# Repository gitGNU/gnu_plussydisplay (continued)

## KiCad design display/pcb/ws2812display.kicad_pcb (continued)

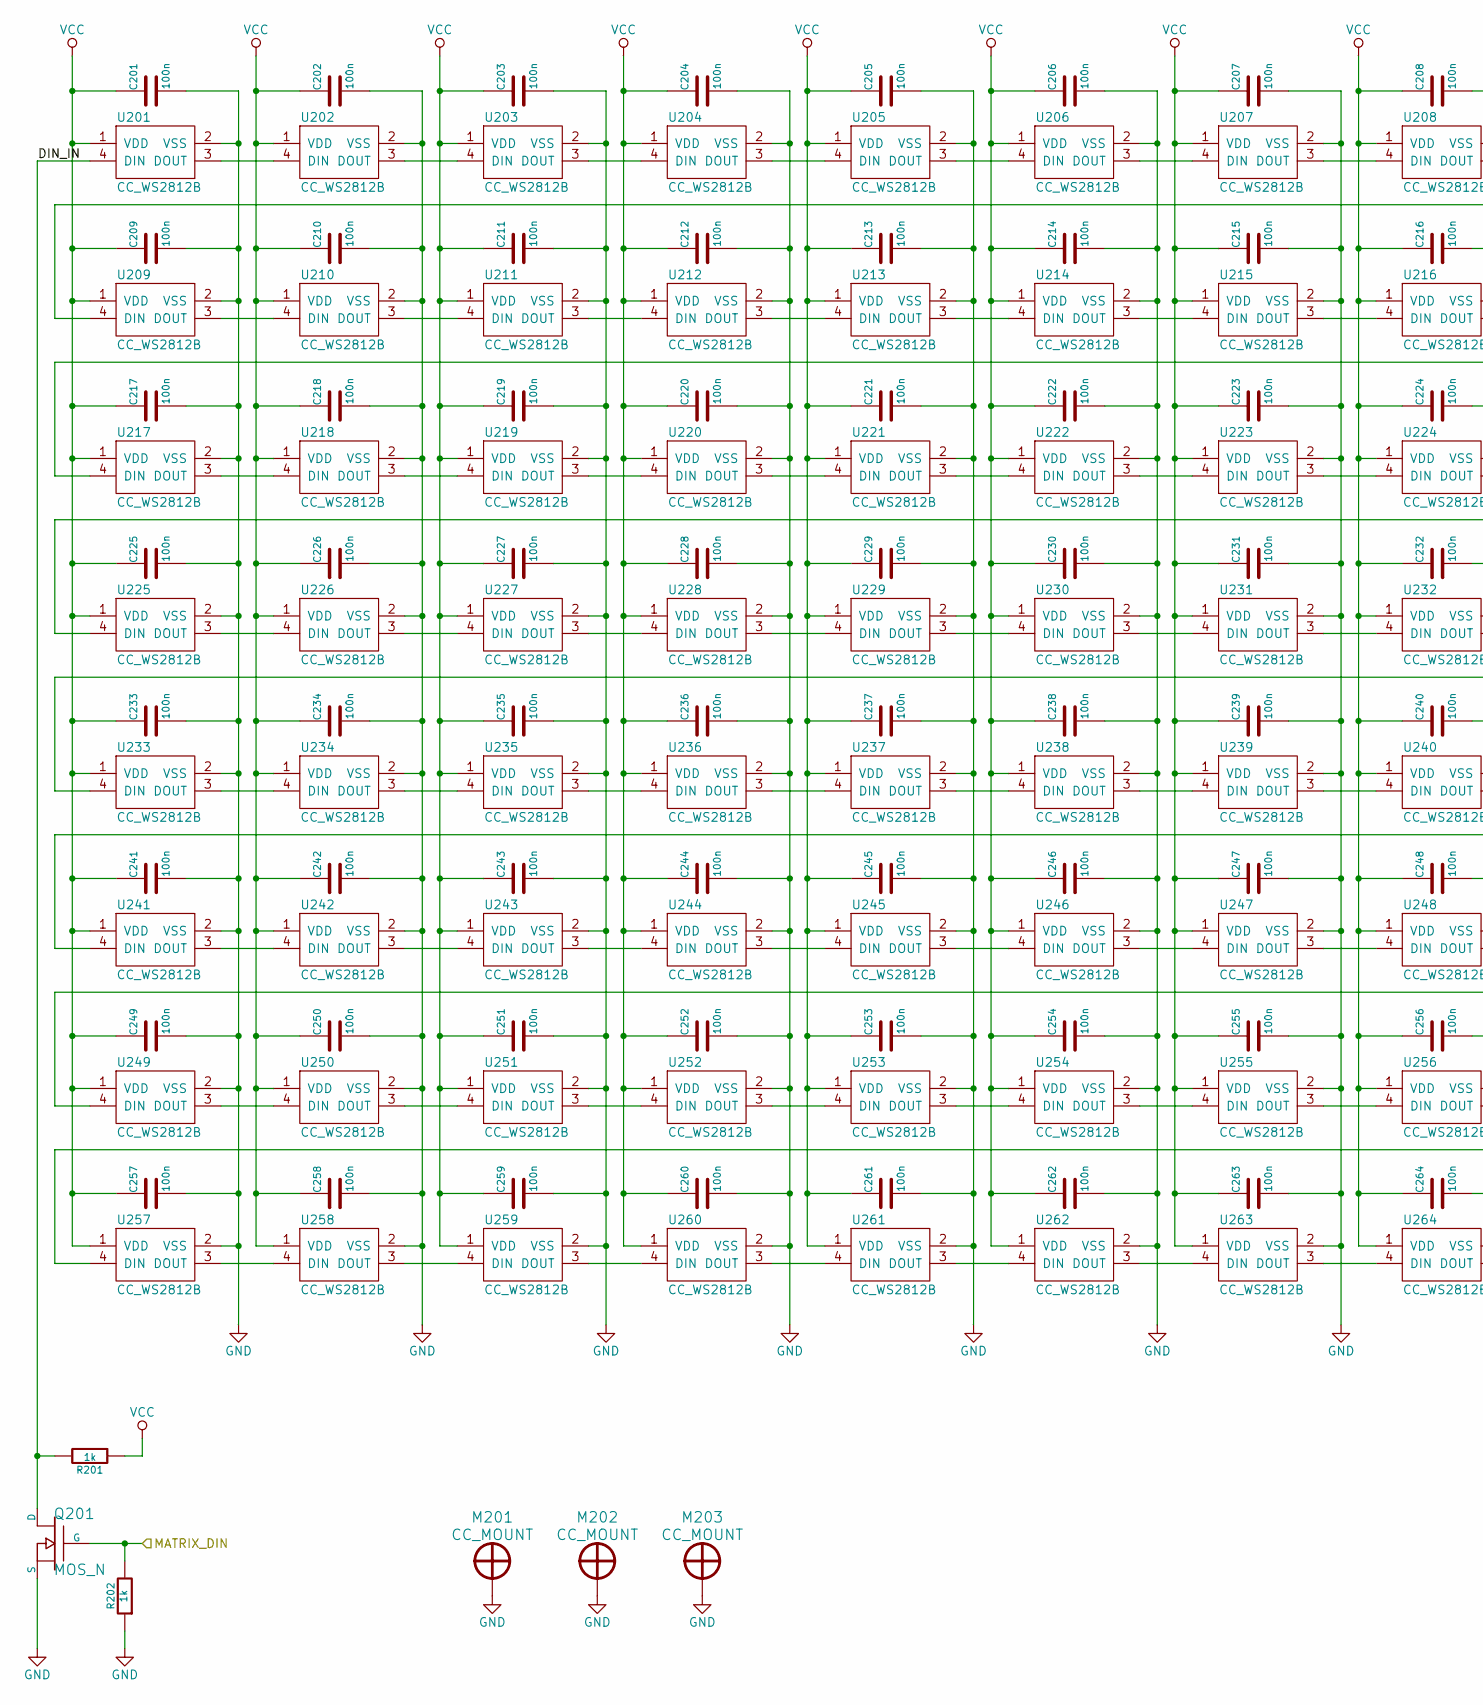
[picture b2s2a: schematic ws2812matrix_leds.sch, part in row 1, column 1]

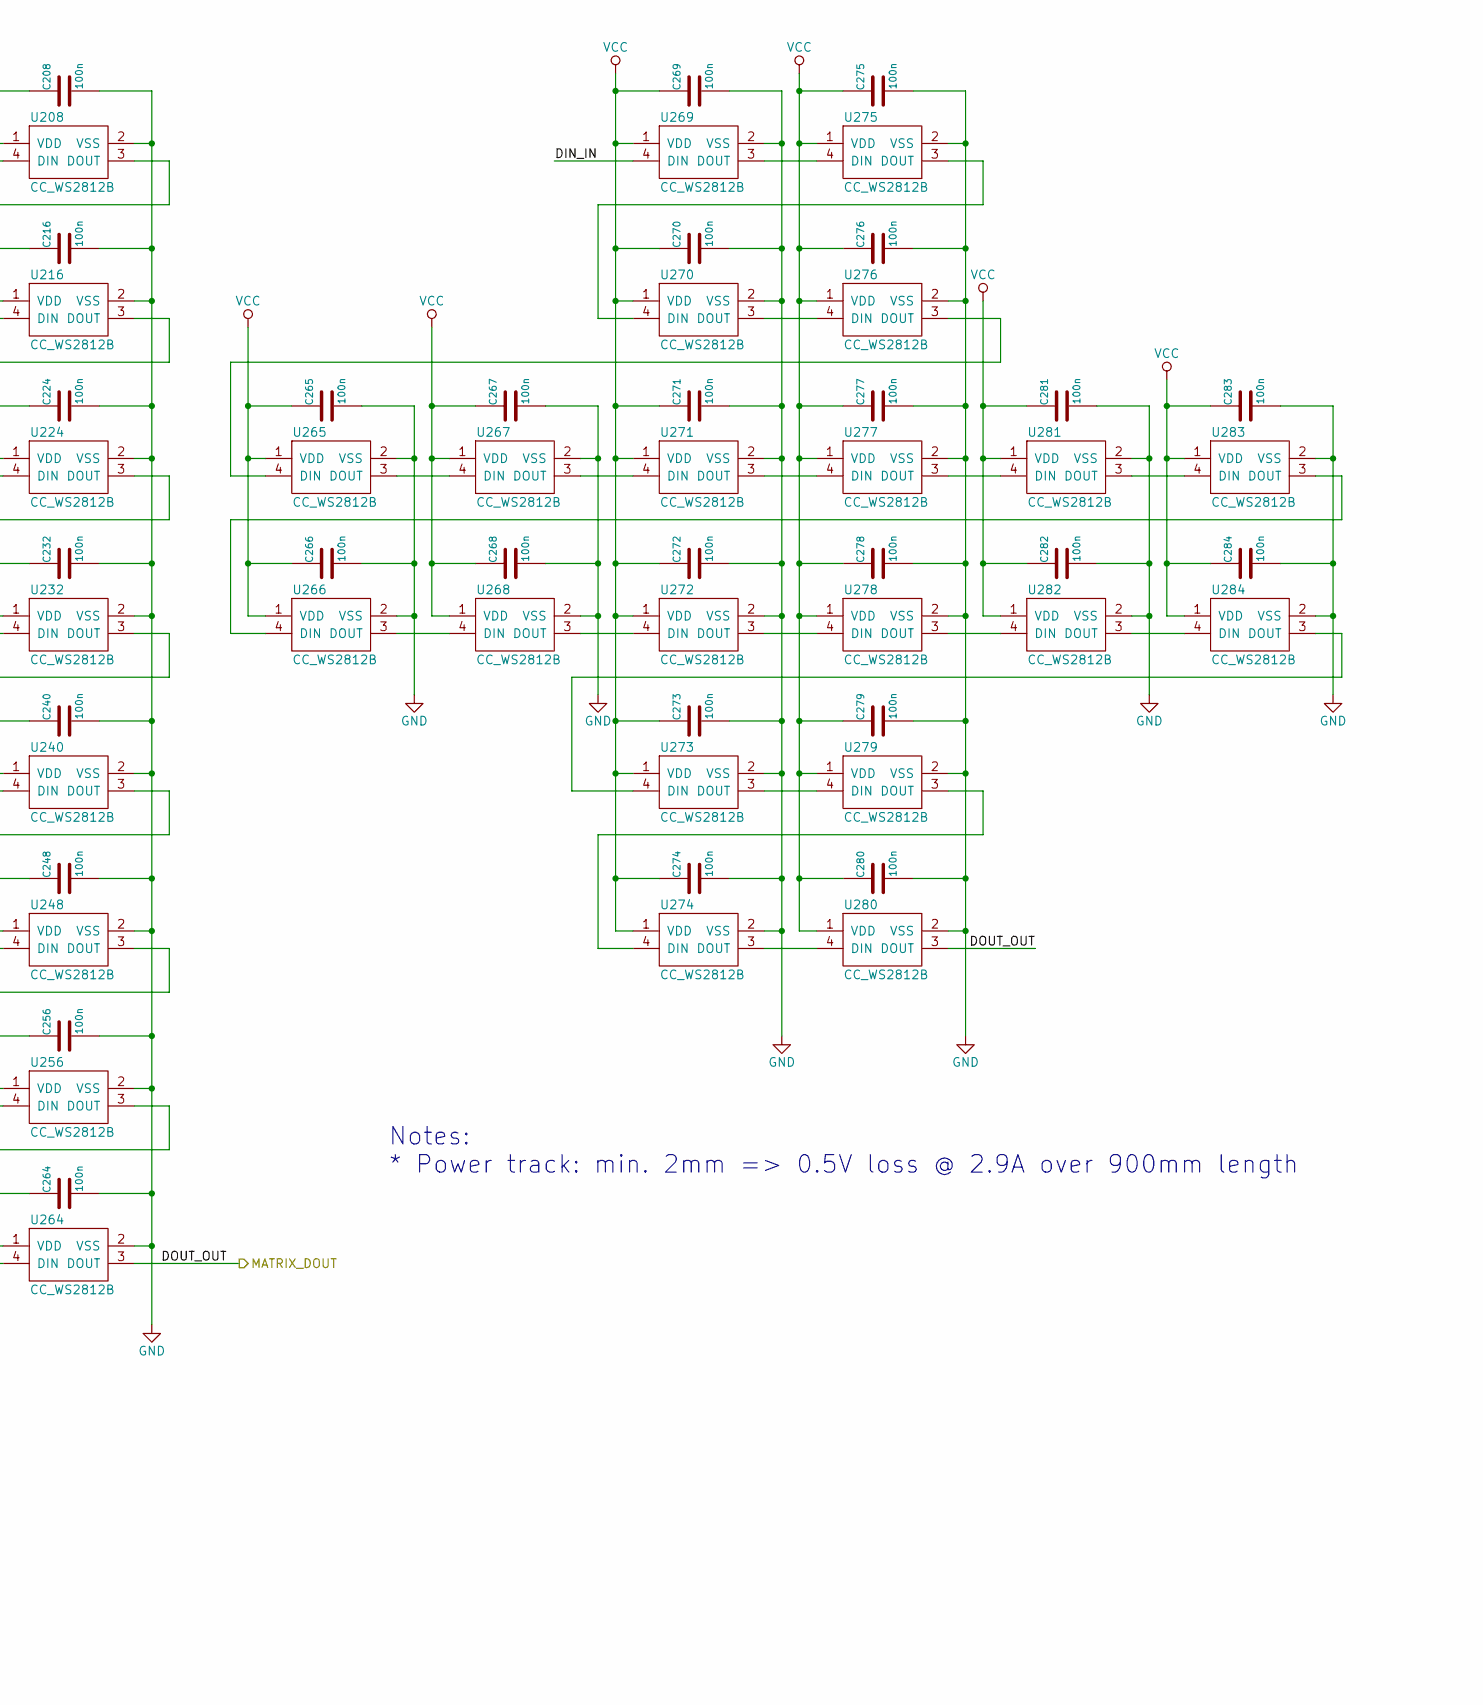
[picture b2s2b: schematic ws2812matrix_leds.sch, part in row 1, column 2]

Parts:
C201, C202, C203, C204, C205, C206, C207, C208, C209, C210, C211, C212, C213, C214, C215, C216, C217, C218, C219, C220, C221, C222, C223, C224, C225, C226, C227, C228, C229, C230, C231, C232, C233, C234, C235, C236, C237, C238, C239, C240, C241, C242, C243, C244, C245, C246, C247, C248, C249, C250, C251, C252, C253, C254, C255, C256, C257, C258, C259, C260, C261, C262, C263, C264, C265, C266, C267, C268, C269, C270, C271, C272, C273, C274, C275, C276, C277, C278, C279, C280, C281, C282, C283, C284: 100n; rcl-cc-0603
M201, M202, M203: CC_MOUNT; CC_MOUNT_PLATED_M3
Q201: MOS_N; CC_SOT23_MOS1
R201, R202: 1k; rcl-cc-0603
U201, U202, U203, U204, U205, U206, U207, U208, U209, U210, U211, U212, U213, U214, U215, U216, U217, U218, U219, U220, U221, U222, U223, U224, U225, U226, U227, U228, U229, U230, U231, U232, U233, U234, U235, U236, U237, U238, U239, U240, U241, U242, U243, U244, U245, U246, U247, U248, U249, U250, U251, U252, U253, U254, U255, U256, U257, U258, U259, U260, U261, U262, U263, U264: CC_WS2812B; WS2812B
U265, U266, U267, U268, U269, U270, U271, U272, U273, U274, U275, U276, U277, U278, U279, U280, U281, U282, U283, U284: CC_WS2812B; WS2812B_8MM

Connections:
/LEDS/DIN_IN: Q201.D, R201.2, U201.4 (DIN), U269.4 (DIN)
GND: C201.2, C202.2, C203.2, C204.2, C205.2, C206.2, C207.2, C208.2, C209.2, C210.2, C211.2, C212.2, C213.2, C214.2, C215.2, C216.2, C217.2, C218.2, C219.2, C220.2, C221.2, C222.2, C223.2, C224.2, C225.2, C226.2, C227.2, C228.2, C229.2, C230.2, C231.2, C232.2, C233.2, C234.2, C235.2, C236.2, C237.2, C238.2, C239.2, C240.2, C241.2, C242.2, C243.2, C244.2, C245.2, C246.2, C247.2, C248.2, C249.2, C250.2, C251.2, C252.2, C253.2, C254.2, C255.2, C256.2, C257.2, C258.2, C259.2, C260.2, C261.2, C262.2, C263.2, C264.2, C265.2, C266.2, C267.2, C268.2, C269.2, C270.2, C271.2, C272.2, C273.2, C274.2, C275.2, C276.2, C277.2, C278.2, C279.2, C280.2, C281.2, C282.2, C283.2, C284.2, M201.1, M202.1, M203.1, Q201.S, R202.1, U201.2 (VSS), U202.2 (VSS), U203.2 (VSS), U204.2 (VSS), U205.2 (VSS), U206.2 (VSS), U207.2 (VSS), U208.2 (VSS), U209.2 (VSS), U210.2 (VSS), U211.2 (VSS), U212.2 (VSS), U213.2 (VSS), U214.2 (VSS), U215.2 (VSS), U216.2 (VSS), U217.2 (VSS), U218.2 (VSS), U219.2 (VSS), U220.2 (VSS), U221.2 (VSS), U222.2 (VSS), U223.2 (VSS), U224.2 (VSS), U225.2 (VSS), U226.2 (VSS), U227.2 (VSS), U228.2 (VSS), U229.2 (VSS), U230.2 (VSS), U231.2 (VSS), U232.2 (VSS), U233.2 (VSS), U234.2 (VSS), U235.2 (VSS), U236.2 (VSS), U237.2 (VSS), U238.2 (VSS), U239.2 (VSS), U240.2 (VSS), U241.2 (VSS), U242.2 (VSS), U243.2 (VSS), U244.2 (VSS), U245.2 (VSS), U246.2 (VSS), U247.2 (VSS), U248.2 (VSS), U249.2 (VSS), U250.2 (VSS), U251.2 (VSS), U252.2 (VSS), U253.2 (VSS), U254.2 (VSS), U255.2 (VSS), U256.2 (VSS), U257.2 (VSS), U258.2 (VSS), U259.2 (VSS), U260.2 (VSS), U261.2 (VSS), U262.2 (VSS), U263.2 (VSS), U264.2 (VSS), U265.2 (VSS), U266.2 (VSS), U267.2 (VSS), U268.2 (VSS), U269.2 (VSS), U270.2 (VSS), U271.2 (VSS), U272.2 (VSS), U273.2 (VSS), U274.2 (VSS), U275.2 (VSS), U276.2 (VSS), U277.2 (VSS), U278.2 (VSS), U279.2 (VSS), U280.2 (VSS), U281.2 (VSS), U282.2 (VSS), U283.2 (VSS), U284.2 (VSS); also elsewhere on the board
unnamed: U201.3 (DOUT), U202.4 (DIN)
unnamed: U202.3 (DOUT), U203.4 (DIN)
unnamed: U203.3 (DOUT), U204.4 (DIN)
unnamed: U204.3 (DOUT), U205.4 (DIN)
unnamed: U205.3 (DOUT), U206.4 (DIN)
unnamed: U206.3 (DOUT), U207.4 (DIN)
unnamed: U207.3 (DOUT), U208.4 (DIN)
unnamed: U208.3 (DOUT), U209.4 (DIN)
unnamed: U209.3 (DOUT), U210.4 (DIN)
unnamed: U210.3 (DOUT), U211.4 (DIN)
unnamed: U211.3 (DOUT), U212.4 (DIN)
unnamed: U212.3 (DOUT), U213.4 (DIN)
unnamed: U213.3 (DOUT), U214.4 (DIN)
unnamed: U214.3 (DOUT), U215.4 (DIN)
unnamed: U215.3 (DOUT), U216.4 (DIN)
unnamed: U216.3 (DOUT), U217.4 (DIN)
unnamed: U217.3 (DOUT), U218.4 (DIN)
unnamed: U218.3 (DOUT), U219.4 (DIN)
unnamed: U219.3 (DOUT), U220.4 (DIN)
unnamed: U220.3 (DOUT), U221.4 (DIN)
unnamed: U221.3 (DOUT), U222.4 (DIN)
unnamed: U222.3 (DOUT), U223.4 (DIN)
unnamed: U223.3 (DOUT), U224.4 (DIN)
unnamed: U224.3 (DOUT), U225.4 (DIN)
unnamed: U225.3 (DOUT), U226.4 (DIN)
unnamed: U226.3 (DOUT), U227.4 (DIN)
unnamed: U227.3 (DOUT), U228.4 (DIN)
unnamed: U228.3 (DOUT), U229.4 (DIN)
unnamed: U229.3 (DOUT), U230.4 (DIN)
unnamed: U230.3 (DOUT), U231.4 (DIN)
unnamed: U231.3 (DOUT), U232.4 (DIN)
unnamed: U232.3 (DOUT), U233.4 (DIN)
unnamed: U233.3 (DOUT), U234.4 (DIN)
unnamed: U234.3 (DOUT), U235.4 (DIN)
unnamed: U235.3 (DOUT), U236.4 (DIN)
unnamed: U236.3 (DOUT), U237.4 (DIN)
unnamed: U237.3 (DOUT), U238.4 (DIN)
unnamed: U238.3 (DOUT), U239.4 (DIN)
unnamed: U239.3 (DOUT), U240.4 (DIN)
unnamed: U240.3 (DOUT), U241.4 (DIN)
unnamed: U241.3 (DOUT), U242.4 (DIN)
unnamed: U242.3 (DOUT), U243.4 (DIN)
unnamed: U243.3 (DOUT), U244.4 (DIN)
unnamed: U244.3 (DOUT), U245.4 (DIN)
unnamed: U245.3 (DOUT), U246.4 (DIN)
unnamed: U246.3 (DOUT), U247.4 (DIN)
unnamed: U247.3 (DOUT), U248.4 (DIN)
unnamed: U248.3 (DOUT), U249.4 (DIN)
unnamed: U249.3 (DOUT), U250.4 (DIN)
unnamed: U250.3 (DOUT), U251.4 (DIN)
unnamed: U251.3 (DOUT), U252.4 (DIN)
unnamed: U252.3 (DOUT), U253.4 (DIN)
unnamed: U253.3 (DOUT), U254.4 (DIN)
unnamed: U254.3 (DOUT), U255.4 (DIN)
unnamed: U255.3 (DOUT), U256.4 (DIN)
unnamed: U256.3 (DOUT), U257.4 (DIN)
unnamed: U257.3 (DOUT), U258.4 (DIN)
unnamed: U258.3 (DOUT), U259.4 (DIN)
unnamed: U259.3 (DOUT), U260.4 (DIN)
unnamed: U260.3 (DOUT), U261.4 (DIN)
unnamed: U261.3 (DOUT), U262.4 (DIN)
unnamed: U262.3 (DOUT), U263.4 (DIN)
unnamed: U263.3 (DOUT), U264.4 (DIN)
unnamed: U265.3 (DOUT), U267.4 (DIN)
unnamed: U265.4 (DIN), U276.3 (DOUT)
unnamed: U266.3 (DOUT), U268.4 (DIN)
unnamed: U266.4 (DIN), U283.3 (DOUT)
unnamed: U267.3 (DOUT), U271.4 (DIN)
unnamed: U268.3 (DOUT), U272.4 (DIN)
unnamed: U269.3 (DOUT), U275.4 (DIN)
unnamed: U270.3 (DOUT), U276.4 (DIN)
unnamed: U270.4 (DIN), U275.3 (DOUT)
unnamed: U271.3 (DOUT), U277.4 (DIN)
unnamed: U272.3 (DOUT), U278.4 (DIN)
unnamed: U273.3 (DOUT), U279.4 (DIN)
unnamed: U273.4 (DIN), U284.3 (DOUT)
unnamed: U274.3 (DOUT), U280.4 (DIN)
unnamed: U274.4 (DIN), U279.3 (DOUT)
unnamed: U277.3 (DOUT), U281.4 (DIN)
unnamed: U278.3 (DOUT), U282.4 (DIN)
unnamed: U281.3 (DOUT), U283.4 (DIN)
unnamed: U282.3 (DOUT), U284.4 (DIN)
VCC: C201.1, C202.1, C203.1, C204.1, C205.1, C206.1, C207.1, C208.1, C209.1, C210.1, C211.1, C212.1, C213.1, C214.1, C215.1, C216.1, C217.1, C218.1, C219.1, C220.1, C221.1, C222.1, C223.1, C224.1, C225.1, C226.1, C227.1, C228.1, C229.1, C230.1, C231.1, C232.1, C233.1, C234.1, C235.1, C236.1, C237.1, C238.1, C239.1, C240.1, C241.1, C242.1, C243.1, C244.1, C245.1, C246.1, C247.1, C248.1, C249.1, C250.1, C251.1, C252.1, C253.1, C254.1, C255.1, C256.1, C257.1, C258.1, C259.1, C260.1, C261.1, C262.1, C263.1, C264.1, C265.1, C266.1, C267.1, C268.1, C269.1, C270.1, C271.1, C272.1, C273.1, C274.1, C275.1, C276.1, C277.1, C278.1, C279.1, C280.1, C281.1, C282.1, C283.1, C284.1, R201.1, U201.1 (VDD), U202.1 (VDD), U203.1 (VDD), U204.1 (VDD), U205.1 (VDD), U206.1 (VDD), U207.1 (VDD), U208.1 (VDD), U209.1 (VDD), U210.1 (VDD), U211.1 (VDD), U212.1 (VDD), U213.1 (VDD), U214.1 (VDD), U215.1 (VDD), U216.1 (VDD), U217.1 (VDD), U218.1 (VDD), U219.1 (VDD), U220.1 (VDD), U221.1 (VDD), U222.1 (VDD), U223.1 (VDD), U224.1 (VDD), U225.1 (VDD), U226.1 (VDD), U227.1 (VDD), U228.1 (VDD), U229.1 (VDD), U230.1 (VDD), U231.1 (VDD), U232.1 (VDD), U233.1 (VDD), U234.1 (VDD), U235.1 (VDD), U236.1 (VDD), U237.1 (VDD), U238.1 (VDD), U239.1 (VDD), U240.1 (VDD), U241.1 (VDD), U242.1 (VDD), U243.1 (VDD), U244.1 (VDD), U245.1 (VDD), U246.1 (VDD), U247.1 (VDD), U248.1 (VDD), U249.1 (VDD), U250.1 (VDD), U251.1 (VDD), U252.1 (VDD), U253.1 (VDD), U254.1 (VDD), U255.1 (VDD), U256.1 (VDD), U257.1 (VDD), U258.1 (VDD), U259.1 (VDD), U260.1 (VDD), U261.1 (VDD), U262.1 (VDD), U263.1 (VDD), U264.1 (VDD), U265.1 (VDD), U266.1 (VDD), U267.1 (VDD), U268.1 (VDD), U269.1 (VDD), U270.1 (VDD), U271.1 (VDD), U272.1 (VDD), U273.1 (VDD), U274.1 (VDD), U275.1 (VDD), U276.1 (VDD), U277.1 (VDD), U278.1 (VDD), U279.1 (VDD), U280.1 (VDD), U281.1 (VDD), U282.1 (VDD), U283.1 (VDD), U284.1 (VDD); also elsewhere on the board
WS2811_DIN: Q201.G, R202.2; also elsewhere on the board
WS2811_DOUT: U264.3 (DOUT), U280.3 (DOUT); also elsewhere on the board

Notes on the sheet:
Notes: * Power track: min. 2mm => 0.5V loss @ 2.9A over 900mm length

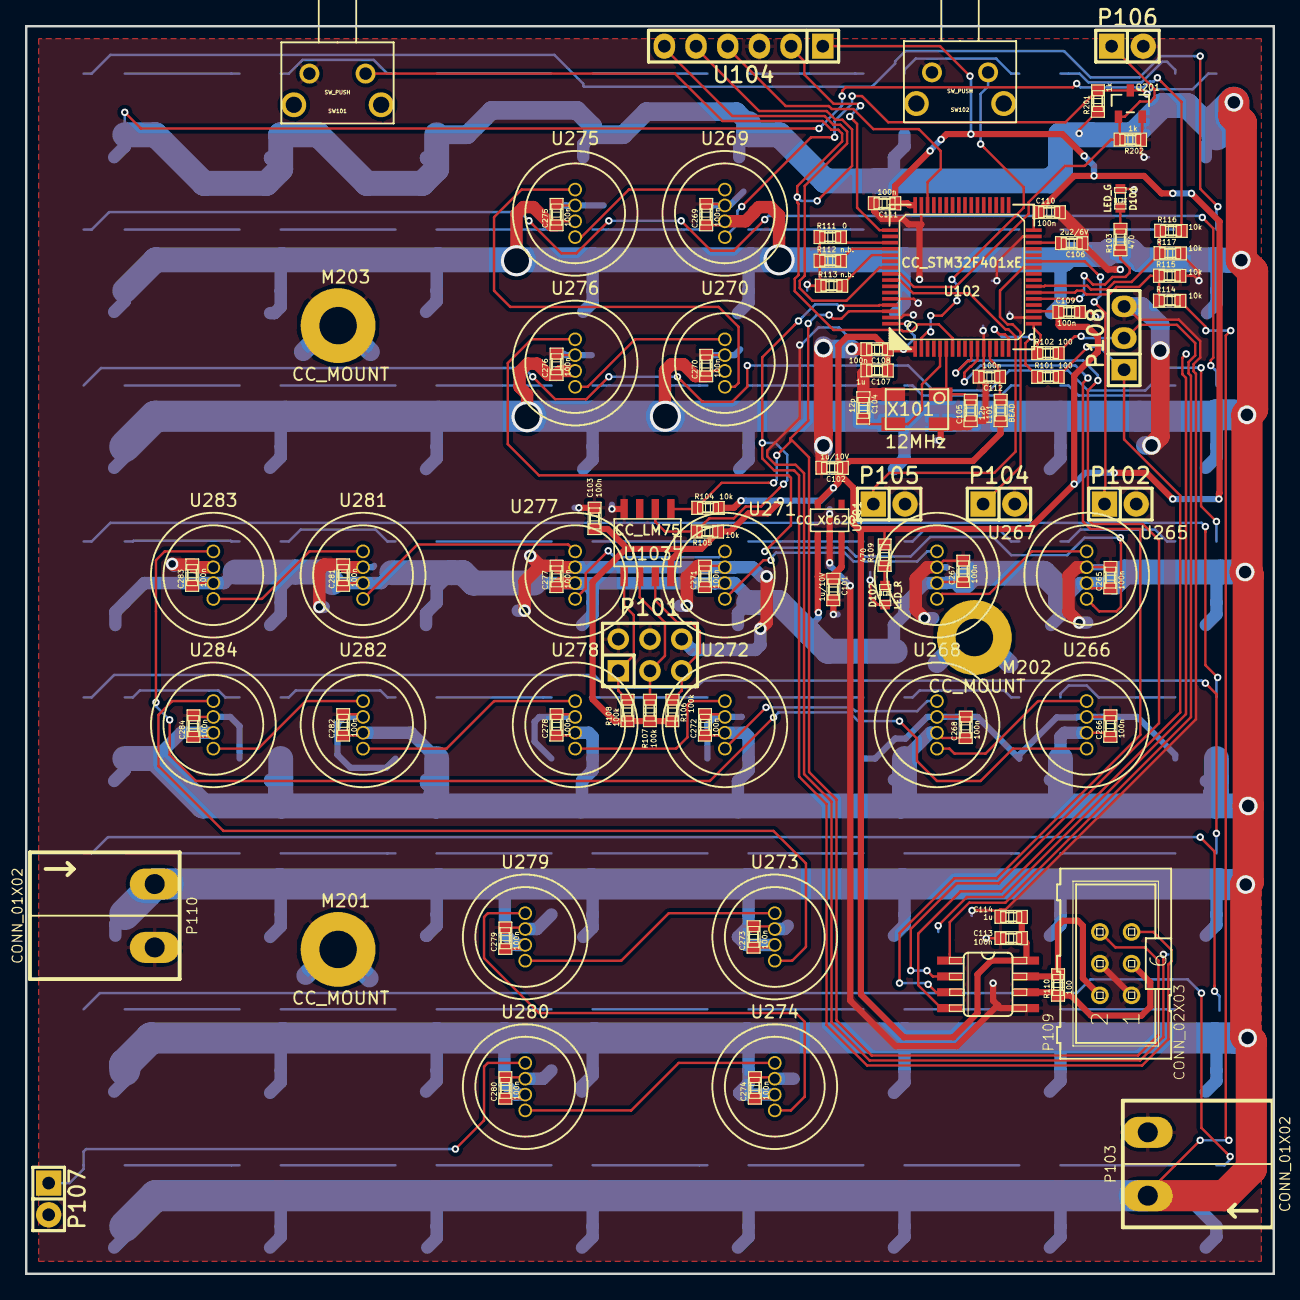
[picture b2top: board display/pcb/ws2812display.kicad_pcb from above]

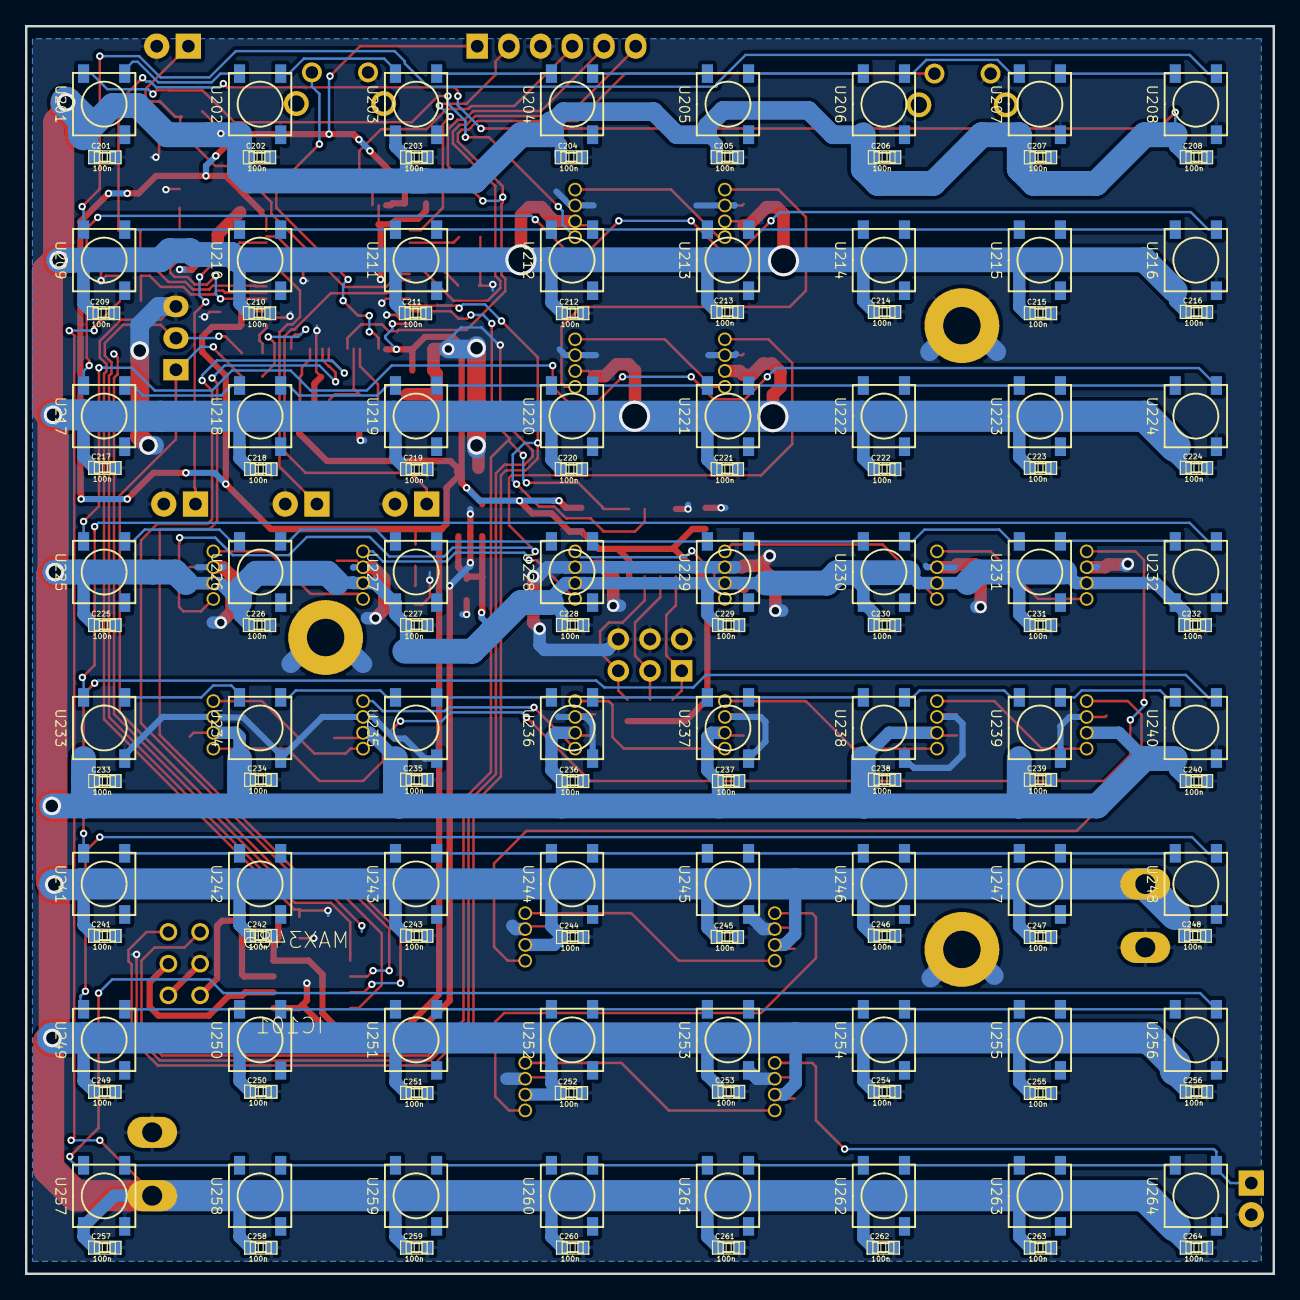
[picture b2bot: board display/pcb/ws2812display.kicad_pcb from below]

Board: 2 copper layers, 100.0 x 100.0 mm, 226 parts (128 on the bottom side), 121 nets.

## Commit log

2015-09-04 initial commit, added part of display design
2015-09-04 added libopencm3
2015-09-04 added (mostly) empty skeleton for uc code - lets an led blink
2015-09-06 implemented simple ws2811 led matrix control and basic demo
2015-09-07 fixed h2rgb conversion
2015-09-09 refactored code to separate animations from ws2811 driver
2015-09-09 added python-based simulation for animations
2015-09-09 added true hsv computation with floats
2015-09-09 added animation time computation
2015-09-09 added missing design files for mechanical frame, updated top plate
2015-09-10 added additional demo animation
2015-09-10 started adding instructions to readme how to add new animations
2015-09-11 fixed bug in led driver
2015-09-11 organize animations using struct-based table
2015-09-11 updated instructions
2015-09-12 fixed cpu architecture
2015-09-12 added eclipse project files
2015-09-12 added usart command interface
2015-09-12 added the necessary usart commands for remote control
2015-09-12 updated ignores
2015-09-12 added missing license statements
2015-09-13 added simple server program and pygame based demo backend
2015-09-15 added all data to reply to 'm' command, added 'r' command for reading complete matrix
2015-09-16 added read (r) command, send complete matrix state as reply to m command
2015-09-16 manage buffer in main program, implemented separate buffer for manual led changes
2015-09-16 added hardware support for server program
2015-09-16 added beaglebone config files and howto
2015-09-17 allow changing animation with user button
2015-09-17 added missing bind config file
2015-09-17 added webserver program, config and setup description
2015-09-18 fixed issue with sscanf writing on wrong memory locations
2015-09-18 minor improvements on server, added init script, fixed hostapd for open wlan
2015-12-12 added pcb files
2016-01-08 implemented hardware version detection and led position remapping for new plussy pcb
2016-02-05 fixed missing button pullup with new hw revision, added some comments
2016-02-05 added constant green figure with very low brightness for photos
2016-02-06 updated config files for new beaglebone black debian jessie images
2016-02-07 added missing systemd init script, removed old one
2016-02-11 added server install instructions for apache cgi mod and uart5
2016-02-11 fixed addressing order for hwversion rev1
2016-02-11 added global brightness scale for moody environments
2016-05-12 added image source and license
2016-05-22 added license statements for config files
2016-05-22 added KiCad backup files to ignore list
2016-05-22 fixed license statements for svg and kicad files
2016-07-09 added v2 display design
2016-08-26 fixed clock setup for current libopencm3 version
2016-08-26 assure reasonable default behavior for unknown hardware revision (fixed crash on null function pointer dereferencing)
2016-08-27 added LED mapping for hardware rev2
2016-08-27 fixed clock setup (APB1 only has 42 MHz max.)
2016-08-27 final pcb design for v2
2016-08-27 added hardware version setting for WS2812B SMD assembly
    WS2812B LEDs have swapped color bits compared to WS2811 controllers
2016-08-29 improved layout of website
2016-08-29 added install instruction for WLAN firmware
2016-09-05 added usb cdcacm loopback device, changed clock to work
2016-09-05 implemented usb command handling like usart
2016-09-05 make makefile verbose
2016-09-05 added bootloadert
2016-09-05 some bootloader debugging
2016-09-06 fixed indexing bug in usb state machine
2016-09-06 removed timing delays in command processing in boot mode
2016-09-06 fixed usb write for blocks larger than 64 bytes
2016-09-06 fixed bootloader bugs
2016-09-09 updated fellowship logo, fixed license
2016-09-09 added captive portal, thanks to Florian
2016-10-16 added hwver 7 (lightctrl) with non-inverted data line
2016-10-23 moved command processing to separate file
2016-10-23 hwversion -> hwinit
2016-10-23 moved hw init code to hwinit
2016-11-19 implemented reply to all clients when colors are changed
2017-03-04 added bottom plate for beagle bone black
2017-03-13 added new laser templates for smd version and beagleboneblack backside
2017-03-13 fixed position errors in top plate v2
2017-03-13 fixed screw positions for bottom plate (separate v2 version)
2017-04-09 added option to switch between ws2811 clock speed modes
2017-04-10 fixed baud rate for new code with changed clock for usb
2017-04-22 added KIBA flyer
